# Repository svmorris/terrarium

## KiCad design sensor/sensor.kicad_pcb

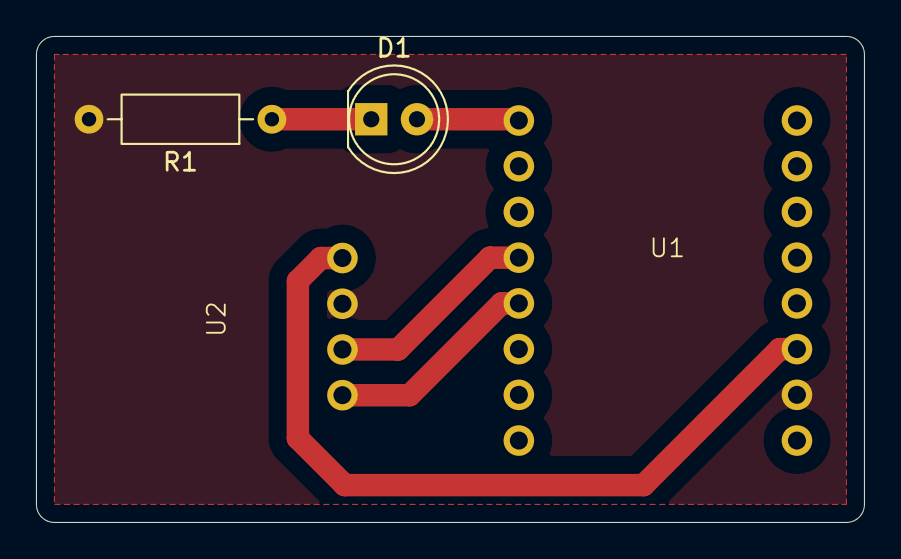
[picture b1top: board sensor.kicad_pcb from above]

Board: 2 copper layers, 46.0 x 27.0 mm, 4 parts (0 on the bottom side), 6 nets.

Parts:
D1: LED; LED_D5.0mm
R1: R; R_Axial_DIN0207_L6.3mm_D2.5mm_P10.16mm_Horizontal
U1: esp32_c3_supermini
U2: SHT31_breakout

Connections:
+3V3: U1.3 (3v3), U2.1 (VIN)
GND: R1.2, U1.2 (GND), U2.2 (GND)
unnamed: D1.2 (A), U1.16 (GPIO21/RXD)
unnamed: D1.1 (K), R1.1
unnamed: U1.12 (GPIO8/SDA/LED), U2.4 (SDA)
unnamed: U1.13 (GPIO9/SCL/BOOT), U2.3 (SCL)

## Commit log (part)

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2026-04-26 Schematic (tested on breadboard) and footprint for the esp
2026-04-26 Managed to 3d print a pcb with copper tape
    (also forgot to push the firmware before this)
